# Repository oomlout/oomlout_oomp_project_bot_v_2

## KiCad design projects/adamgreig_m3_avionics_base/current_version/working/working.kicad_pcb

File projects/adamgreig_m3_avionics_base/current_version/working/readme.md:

# m3_avionics
 
## summary 
* id: adamgreig_m3_avionics_base
* user: adamgreig
* name: m3_avionics
* board: base
* repo: https://github.com/adamgreig/m3-avionics
* src_file_repo_kicad_pcb: m3base/base.kicad_pcb
* src_file_repo_kicad_pcb_link: https://github.com/adamgreig/m3-avionics/tree/master/m3base/base.kicad_pcb

* src_file_repo_sch: m3base/base.sch
* src_file_repo_sch_link: https://github.com/adamgreig/m3-avionics/tree/master/m3base/base.sch
* full details link: https://github.com/oomlout/oomlout_oomp_project_bot_v_2/tree/main/projects/adamgreig_m3_avionics_base/current_version/working  

## schematic  
  
[schematic (pdf)](working_schematic.pdf) 

## pcb  

[board (pdf)](working.pdf)  

## working_bom
| Id | Designator | Footprint | Quantity | Designation | Supplier and ref |  | None | 
| --- | --- | --- | --- | --- | --- | --- | --- | 
| 1 | C4,C5 | 0603-L | 2 | 2u2 |  |  | [''] | 
| 2 | C6 | 0603-L | 1 | 1u |  |  | [''] | 
| 3 | C7,C8,C11,C12,C13,C16,C1 | 0603-L | 7 | 100n |  |  | [''] | 
| 4 | R2 | 0603-L | 1 | 4K7 |  |  | [''] | 
| 5 | R3 | 0603-L | 1 | 10K |  |  | [''] | 
| 6 | C2,C3 | 0603-L | 2 | 10p |  |  | [''] | 
| 7 | IC1 | LQFP-64 | 1 | STM32F405RxTx |  |  | [''] | 
| 8 | IC2 | DFN-8-EP-MICROCHIP | 1 | MCP2562 |  |  | [''] | 
| 9 | J1 | TFML-110-02-L-D | 1 | WEST TOP |  |  | [''] | 
| 10 | J2 | TFML-110-02-L-D | 1 | EAST TOP |  |  | [''] | 
| 11 | R1 | 0603-L | 1 | 100R |  |  | [''] | 
| 12 | R5 | 0603-L | 1 | 120R |  |  | [''] | 
| 13 | Y1 | XTAL-20x16 | 1 | 26MHz |  |  | [''] | 
| 14 | D1,D2,D3,D4,D5,D6,D7,D8,D9,D10,D11,D12 | 0402 | 12 | ESD_DIODE |  |  | [''] | 
| 15 | C15 | 0603-L | 1 | 4u7 |  |  | [''] | 
| 16 | J5 | B02B-PASK | 1 | PYRO1 |  |  | [''] | 
| 17 | J6 | B02B-PASK | 1 | PYRO3 |  |  | [''] | 
| 18 | J7 | B02B-PASK | 1 | ARM |  |  | [''] | 
| 19 | J8 | B02B-PASK | 1 | PYRO2 |  |  | [''] | 
| 20 | J9 | B02B-PASK | 1 | PYRO4 |  |  | [''] | 
| 21 | J10 | B02B-PASK | 1 | PWR |  |  | [''] | 
| 22 | J11 | B02B-PASK | 1 | CHG |  |  | [''] | 
| 23 | J12 | B02B-PASK | 1 | CAM |  |  | [''] | 
| 24 | J13 | B04B-PASK | 1 | USB |  |  | [''] | 
| 25 | P1 | TC2030-NL | 1 | SWD_TC |  |  | [''] | 
| 26 | R4 | 0603-L | 1 | 1K |  |  | [''] | 

## bom_schematic
| Ref | Qnty | Value | Cmp name | Footprint | Description | Vendor | DNP | 
| --- | --- | --- | --- | --- | --- | --- | --- | 
| C1, C7, C8, C11, C12, C13, C16 | 7 | 100n | C_Small | Capacitors_SMD:C_0603 |  |  |  | 
| C2, C3 | 2 | 10p | C_Small | Capacitors_SMD:C_0603 |  |  |  | 
| C4, C5 | 2 | 2u2 | C_Small | Capacitors_SMD:C_0603 |  |  |  | 
| C6 | 1 | 1u | C_Small | Capacitors_SMD:C_0603 |  |  |  | 
| C15 | 1 | 4u7 | C_Small | Capacitors_SMD:C_0603 |  |  |  | 
| D1, D2, D3, D4, D5, D6, D7, D8, D9, D10, D11, D12 | 12 | ESD_DIODE | ESD_DIODE | agg:0402 |  |  |  | 
| IC1 | 1 | STM32F405RxTx | STM32F405RxTx | agg:LQFP-64 |  |  |  | 
| IC2 | 1 | MCP2562 | MCP2562 | agg:DFN-8-EP-MICROCHIP |  |  |  | 
| J1 | 1 | WEST TOP | CONN_02x10 | agg:TFML-110-02-L-D |  |  |  | 
| J2 | 1 | EAST TOP | CONN_02x10 | agg:TFML-110-02-L-D |  |  |  | 
| J5 | 1 | PYRO1 | CONN_01x02 | agg:B02B-PASK |  |  |  | 
| J6 | 1 | PYRO3 | CONN_01x02 | agg:B02B-PASK |  |  |  | 
| J7 | 1 | ARM | CONN_01x02 | agg:B02B-PASK |  |  |  | 
| J8 | 1 | PYRO2 | CONN_01x02 | agg:B02B-PASK |  |  |  | 
| J9 | 1 | PYRO4 | CONN_01x02 | agg:B02B-PASK |  |  |  | 
| J10 | 1 | PWR | CONN_01x02 | agg:B02B-PASK |  |  |  | 
| J11 | 1 | CHG | CONN_01x02 | agg:B02B-PASK |  |  |  | 
| J12 | 1 | CAM | CONN_01x02 | agg:B02B-PASK |  |  |  | 
| J13 | 1 | USB | CONN_01x04 | agg:B04B-PASK |  |  |  | 
| P1 | 1 | SWD_TC | SWD_TC | agg:TC2030-NL |  |  |  | 
| R1 | 1 | 100R | R | Resistors_SMD:R_0603 |  |  |  | 
| R2 | 1 | 4K7 | R | Resistors_SMD:R_0603 |  |  |  | 
| R3 | 1 | 10K | R | Resistors_SMD:R_0603 |  |  |  | 
| R4 | 1 | 1K | R | Resistors_SMD:R_0603 |  |  |  | 
| R5 | 1 | 120R | R | Resistors_SMD:R_0603 |  |  |  | 
| Y1 | 1 | 26MHz | XTAL | agg:XTAL-20x16 |  |  |  |

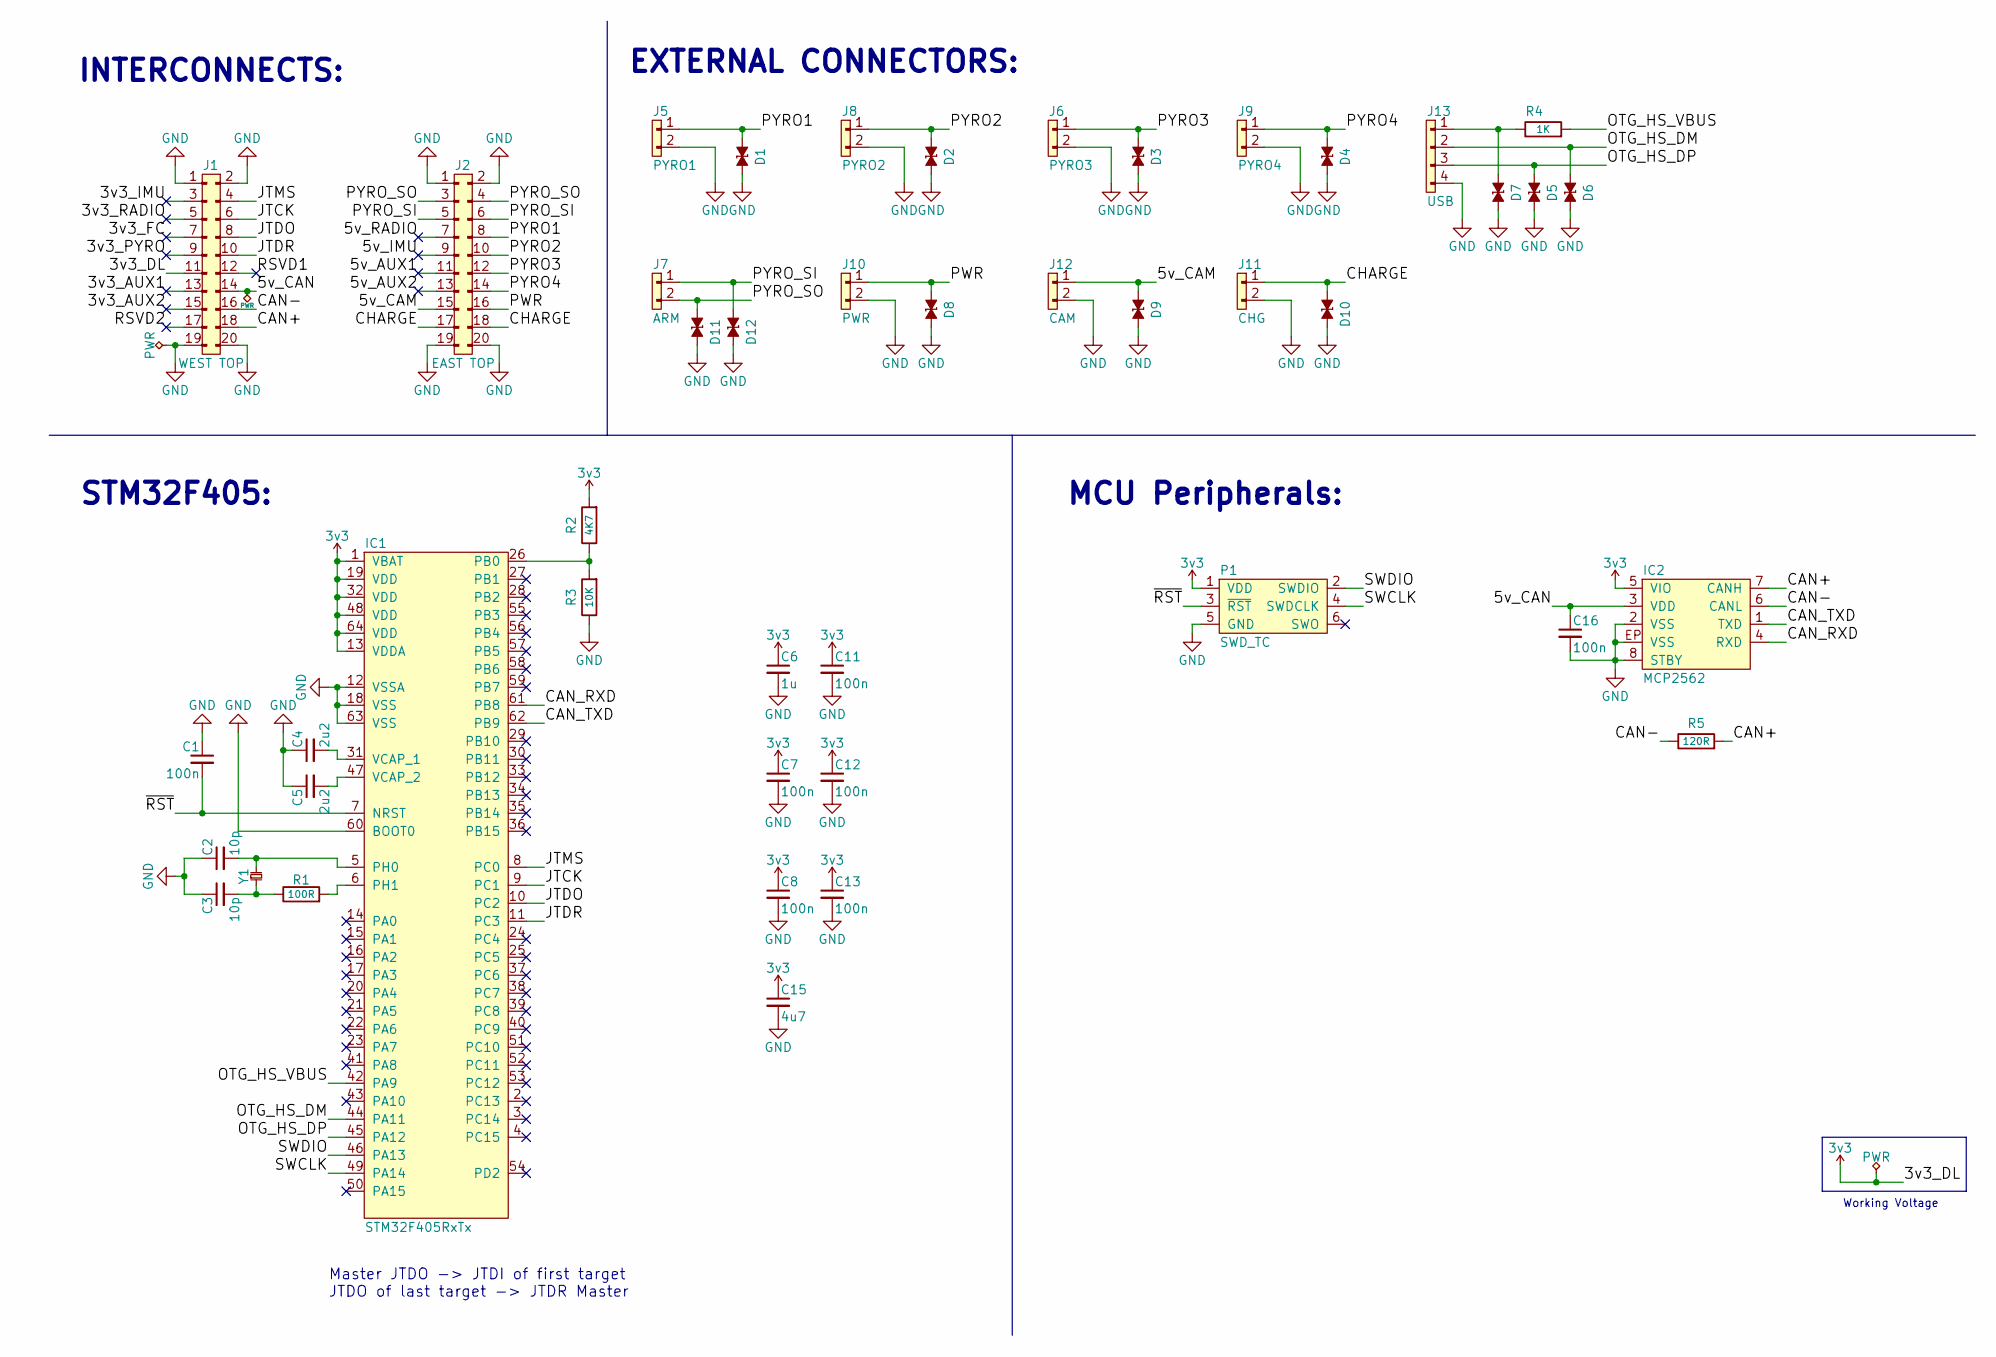
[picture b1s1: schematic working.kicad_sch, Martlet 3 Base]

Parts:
C1, C7, C8, C11, C12, C13, C16: 100n; C_0603; Farnell 2496834
C2, C3: 10p; C_0603; Farnell 2309035
C4, C5: 2u2; C_0603; Farnell 1797012
C6: 1u; C_0603; Farnell 1865556
C15: 4u7; C_0603; Farnell 2496930
D1, D2, D3, D4, D5, D6, D7, D8, D9, D10, D11, D12: ESD_DIODE; 0402; Farnell 2368169
IC1: STM32F405RxTx; LQFP-64; Farnell 2064363
IC2: MCP2562; DFN-8-EP-MICROCHIP; Farnell 2448755
J1: WEST TOP; TFML-110-02-L-D
J2: EAST TOP; TFML-110-02-L-D
J5: PYRO1; B02B-PASK; Farnell 1830734
J6: PYRO3; B02B-PASK; Farnell 1830734
J7: ARM; B02B-PASK; Farnell 1830734
J8: PYRO2; B02B-PASK; Farnell 1830734
J9: PYRO4; B02B-PASK; Farnell 1830734
J10: PWR; B02B-PASK; Farnell 1830734
J11: CHG; B02B-PASK; Farnell 1830734
J12: CAM; B02B-PASK; Farnell 1830734
J13: USB; B04B-PASK; Farnell 1830737
P1: SWD_TC; TC2030-NL
R1: 100R; R_0603; Farnell 2502395
R2: 4K7; R_0603; Farnell 2502463
R3: 10K; R_0603; Farnell 9238603
R4: 1K; R_0603; Farnell 2309108
R5: 120R; R_0603; Farnell 9238379
Y1: 26MHz; XTAL-20x16; Farnell 2506952

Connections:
3v3: C6.1, C7.1, C8.1, C11.1, C12.1, C13.1, C15.1, IC1.1 (VBAT), IC1.13 (VDDA), IC1.19 (VDD), IC1.32 (VDD), IC1.48 (VDD), IC1.64 (VDD), IC2.5 (VIO), J1.11, P1.1 (VDD), R2.2
/3v3_AUX1: J1.13
/3v3_AUX2: J1.15
/3v3_FC: J1.7
/3v3_IMU: J1.3
/3v3_PYRO: J1.9
/3v3_RADIO: J1.5
/5v_AUX1: J2.11
/5v_AUX2: J2.13
/5v_CAM: D9.1, J2.15, J12.1
/5v_CAN: C16.1, IC2.3 (VDD), J1.14
/5v_IMU: J2.9
/5v_RADIO: J2.7
/CAN+: IC2.7 (CANH), J1.18, R5.2
/CAN-: IC2.6 (CANL), J1.16, R5.1
/CAN_RXD: IC1.61 (PB8), IC2.4 (RXD)
/CAN_TXD: IC1.62 (PB9), IC2.1 (TXD)
/CHARGE: D10.1, J2.17, J2.18, J11.1
/JTCK: IC1.9 (PC1), J1.6
/JTDO: IC1.10 (PC2), J1.8
/JTDR: IC1.11 (PC3), J1.10
/JTMS: IC1.8 (PC0), J1.4
/OTG_HS_DM: D6.1, IC1.44 (PA11), J13.2
/OTG_HS_DP: D5.1, IC1.45 (PA12), J13.3
/OTG_HS_VBUS: IC1.42 (PA9), R4.2
/PWR: D8.1, J2.16, J10.1
/PYRO1: D1.1, J2.8, J5.1
/PYRO2: D2.1, J2.10, J8.1
/PYRO3: D3.1, J2.12, J6.1
/PYRO4: D4.1, J2.14, J9.1
/PYRO_SI: D12.1, J2.5, J2.6, J7.1
/PYRO_SO: D11.1, J2.3, J2.4, J7.2
/RSVD1: J1.12
/RSVD2: J1.17
/SWCLK: IC1.49 (PA14), P1.4 (SWDCLK)
/SWDIO: IC1.46 (PA13), P1.2 (SWDIO)
/~RST: C1.2, IC1.7 (NRST), P1.3 (~RST)
GND: C1.1, C2.1, C3.1, C4.1, C5.1, C6.2, C7.2, C8.2, C11.2, C12.2, C13.2, C15.2, C16.2, D1.2, D2.2, D3.2, D4.2, D5.2, D6.2, D7.2, D8.2, D9.2, D10.2, D11.2, D12.2, IC1.12 (VSSA), IC1.18 (VSS), IC1.60 (BOOT0), IC1.63 (VSS), IC2.2 (VSS), IC2.8 (STBY), IC2.EP (VSS), J1.1, J1.2, J1.19, J1.20, J2.1, J2.2, J2.19, J2.20, J5.2, J6.2, J8.2, J9.2, J10.2, J11.2, J12.2, J13.4, P1.5 (GND), R3.1
unnamed: C2.2, IC1.5 (PH0), Y1.2
unnamed: C3.2, R1.1, Y1.1
unnamed: C4.2, IC1.31 (VCAP_1)
unnamed: C5.2, IC1.47 (VCAP_2)
unnamed: D7.1, J13.1, R4.1
unnamed: IC1.6 (PH1), R1.2
unnamed: IC1.26 (PB0), R2.1, R3.2

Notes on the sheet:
STM32F405:
INTERCONNECTS:
MCU Peripherals:
EXTERNAL CONNECTORS:
Master JTDO -> JTDI of first target JTDO of last target -> JTDR Master
Working Voltage

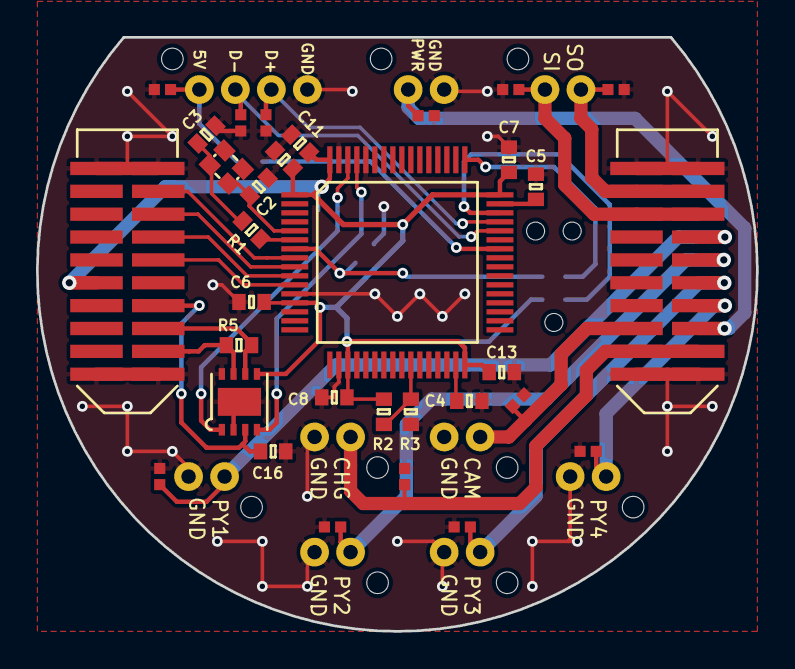
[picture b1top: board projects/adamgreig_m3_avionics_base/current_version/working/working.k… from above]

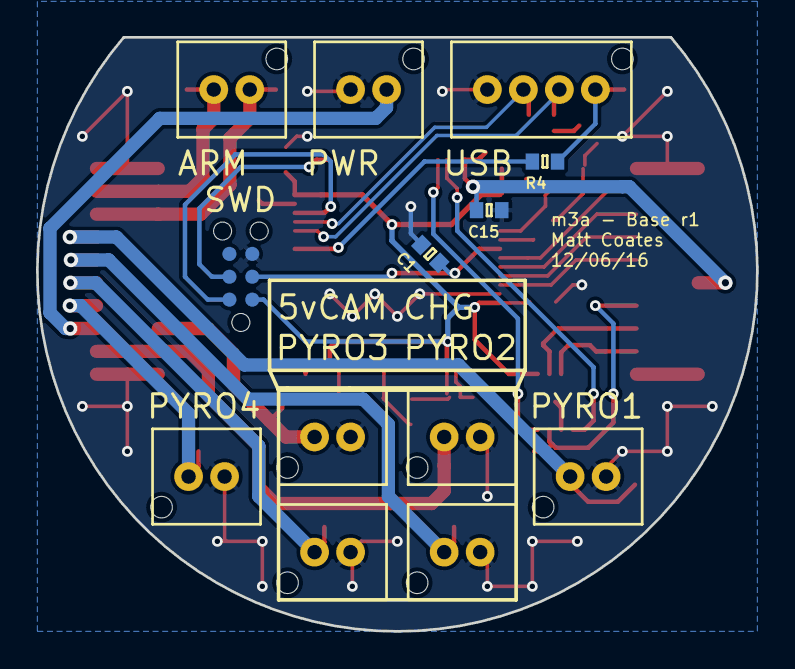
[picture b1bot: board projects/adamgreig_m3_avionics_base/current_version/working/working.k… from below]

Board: 2 copper layers, 40.0 x 33.0 mm, 45 parts (13 on the bottom side), 33 nets.

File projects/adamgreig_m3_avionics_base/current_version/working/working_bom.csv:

"Id";"Designator";"Footprint";"Quantity";"Designation";"Supplier and ref";
1;"C4,C5";"0603-L";2;"2u2";;;
2;"C6";"0603-L";1;"1u";;;
3;"C7,C8,C11,C12,C13,C16,C1";"0603-L";7;"100n";;;
4;"R2";"0603-L";1;"4K7";;;
5;"R3";"0603-L";1;"10K";;;
6;"C2,C3";"0603-L";2;"10p";;;
7;"IC1";"LQFP-64";1;"STM32F405RxTx";;;
8;"IC2";"DFN-8-EP-MICROCHIP";1;"MCP2562";;;
9;"J1";"TFML-110-02-L-D";1;"WEST TOP";;;
10;"J2";"TFML-110-02-L-D";1;"EAST TOP";;;
11;"R1";"0603-L";1;"100R";;;
12;"R5";"0603-L";1;"120R";;;
13;"Y1";"XTAL-20x16";1;"26MHz";;;
14;"D1,D2,D3,D4,D5,D6,D7,D8,D9,D10,D11,D12";"0402";12;"ESD_DIODE";;;
15;"C15";"0603-L";1;"4u7";;;
16;"J5";"B02B-PASK";1;"PYRO1";;;
17;"J6";"B02B-PASK";1;"PYRO3";;;
18;"J7";"B02B-PASK";1;"ARM";;;
19;"J8";"B02B-PASK";1;"PYRO2";;;
20;"J9";"B02B-PASK";1;"PYRO4";;;
21;"J10";"B02B-PASK";1;"PWR";;;
22;"J11";"B02B-PASK";1;"CHG";;;
23;"J12";"B02B-PASK";1;"CAM";;;
24;"J13";"B04B-PASK";1;"USB";;;
25;"P1";"TC2030-NL";1;"SWD_TC";;;
26;"R4";"0603-L";1;"1K";;;

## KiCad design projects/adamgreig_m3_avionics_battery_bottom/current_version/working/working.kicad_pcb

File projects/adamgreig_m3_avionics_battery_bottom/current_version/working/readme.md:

# m3_avionics
 
## summary 
* id: adamgreig_m3_avionics_battery_bottom
* user: adamgreig
* name: m3_avionics
* board: battery_bottom
* repo: https://github.com/adamgreig/m3-avionics
* src_file_repo_kicad_pcb: m3psu/pcb/Battery-Bottom/Battery-Bottom.kicad_pcb
* src_file_repo_kicad_pcb_link: https://github.com/adamgreig/m3-avionics/tree/master/m3psu/pcb/Battery-Bottom/Battery-Bottom.kicad_pcb

* src_file_repo_sch: m3psu/pcb/Battery-Bottom/Battery-Bottom.sch
* src_file_repo_sch_link: https://github.com/adamgreig/m3-avionics/tree/master/m3psu/pcb/Battery-Bottom/Battery-Bottom.sch
* full details link: https://github.com/oomlout/oomlout_oomp_project_bot_v_2/tree/main/projects/adamgreig_m3_avionics_battery_bottom/current_version/working  

## schematic  
  
[schematic (pdf)](working_schematic.pdf) 

## pcb  

[board (pdf)](working.pdf)  

## working_bom
| Id | Designator | Footprint | Quantity | Designation | Supplier and ref |  | None | 
| --- | --- | --- | --- | --- | --- | --- | --- | 
| 1 | J1 | Socket_Strip_Straight_1x01 | 1 | BATT_CENTRE_TAP |  |  | [''] | 
| 2 | J3 | TFML-110-02-L-D | 1 | WEST TOP |  |  | [''] | 
| 3 | J5 | TFML-110-02-L-D | 1 | EAST TOP |  |  | [''] | 
| 4 | J2 | Socket_Strip_Straight_1x02 | 1 | BATT |  |  | [''] | 
| 5 | J4 | SFML-110-02-L-D-LC | 1 | WEST BOT |  |  | [''] | 
| 6 | J6 | SFML-110-02-L-D-LC | 1 | EAST BOT |  |  | [''] | 
| 7 | J7 | SFML-105-02-L-D-LC | 1 | NORTH BOT |  |  | [''] | 

## bom_schematic
| Ref | Qnty | Value | Cmp name | Footprint | Description | Vendor | DNP | 
| --- | --- | --- | --- | --- | --- | --- | --- | 
| J1 | 1 | BATT_CENTRE_TAP | CONN_01x01 | Socket_Strips:Socket_Strip_Straight_1x01 |  |  |  | 
| J2 | 1 | BATT | CONN_01x02 | Socket_Strips:Socket_Strip_Straight_1x02 |  |  |  | 
| J3 | 1 | WEST TOP | CONN_02x10 | agg:TFML-110-02-L-D |  |  |  | 
| J4 | 1 | WEST BOT | CONN_02x10 | agg:SFML-110-02-L-D-LC |  |  |  | 
| J5 | 1 | EAST TOP | CONN_02x10 | agg:TFML-110-02-L-D |  |  |  | 
| J6 | 1 | EAST BOT | CONN_02x10 | agg:SFML-110-02-L-D-LC |  |  |  | 
| J7 | 1 | NORTH BOT | CONN_02x05 | agg:SFML-105-02-L-D-LC |  |  |  |

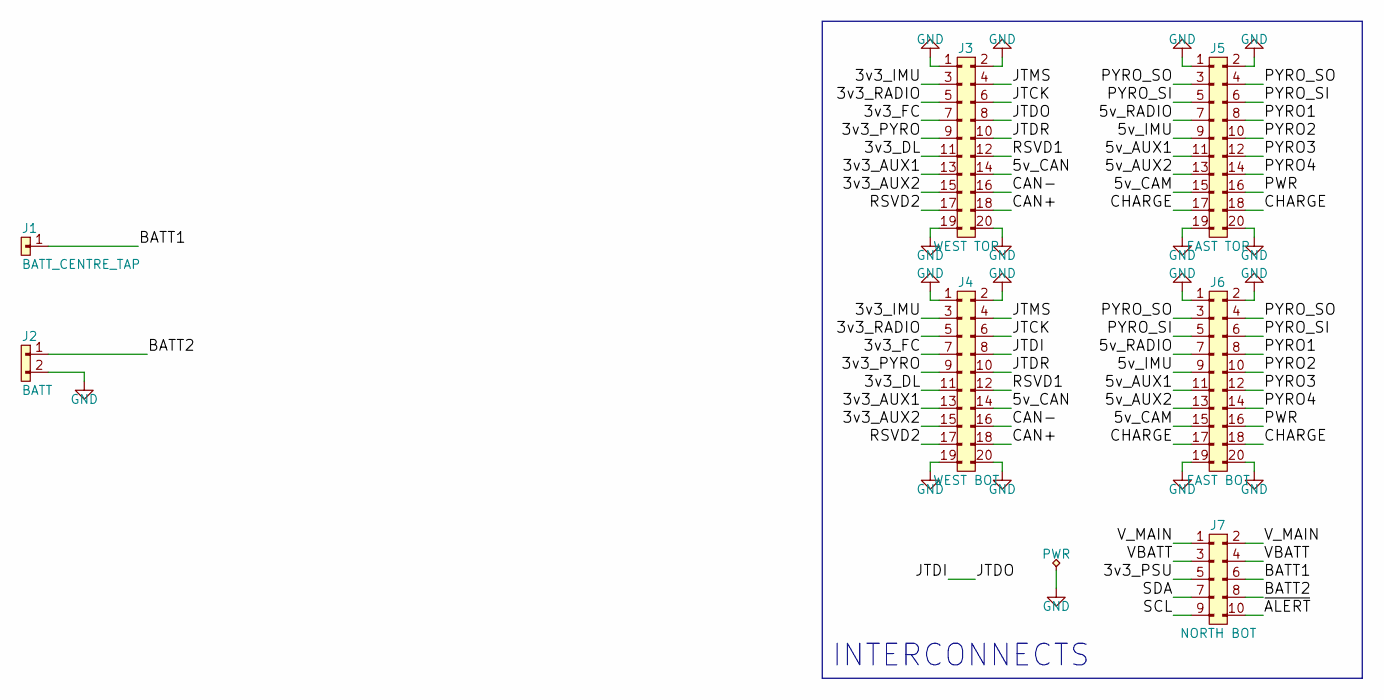
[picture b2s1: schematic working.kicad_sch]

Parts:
J1: BATT_CENTRE_TAP; Socket_Strip_Straight_1x01
J2: BATT; Socket_Strip_Straight_1x02
J3: WEST TOP; TFML-110-02-L-D
J4: WEST BOT; SFML-110-02-L-D-LC
J5: EAST TOP; TFML-110-02-L-D
J6: EAST BOT; SFML-110-02-L-D-LC
J7: NORTH BOT; SFML-105-02-L-D-LC

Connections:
/3v3_AUX1: J3.13, J4.13
/3v3_AUX2: J3.15, J4.15
/3v3_DL: J3.11, J4.11
/3v3_FC: J3.7, J4.7
/3v3_IMU: J3.3, J4.3
/3v3_PSU: J7.5
/3v3_PYRO: J3.9, J4.9
/3v3_RADIO: J3.5, J4.5
/5v_AUX1: J5.11, J6.11
/5v_AUX2: J5.13, J6.13
/5v_CAM: J5.15, J6.15
/5v_CAN: J3.14, J4.14
/5v_IMU: J5.9, J6.9
/5v_RADIO: J5.7, J6.7
/BATT1: J1.1, J7.6
/BATT2: J2.1, J7.8
/CAN+: J3.18, J4.18
/CAN-: J3.16, J4.16
/CHARGE: J5.17, J5.18, J6.17, J6.18
/JTCK: J3.6, J4.6
/JTDI: J3.8, J4.8
/JTDR: J3.10, J4.10
/JTMS: J3.4, J4.4
/PWR: J5.16, J6.16
/PYRO1: J5.8, J6.8
/PYRO2: J5.10, J6.10
/PYRO3: J5.12, J6.12
/PYRO4: J5.14, J6.14
/PYRO_SI: J5.5, J5.6, J6.5, J6.6
/PYRO_SO: J5.3, J5.4, J6.3, J6.4
/RSVD1: J3.12, J4.12
/RSVD2: J3.17, J4.17
/SCL: J7.9
/SDA: J7.7
/VBATT: J7.3, J7.4
/V_MAIN: J7.1, J7.2
/~ALERT: J7.10
GND: J2.2, J3.1, J3.2, J3.19, J3.20, J4.1, J4.2, J4.19, J4.20, J5.1, J5.2, J5.19, J5.20, J6.1, J6.2, J6.19, J6.20

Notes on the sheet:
INTERCONNECTS

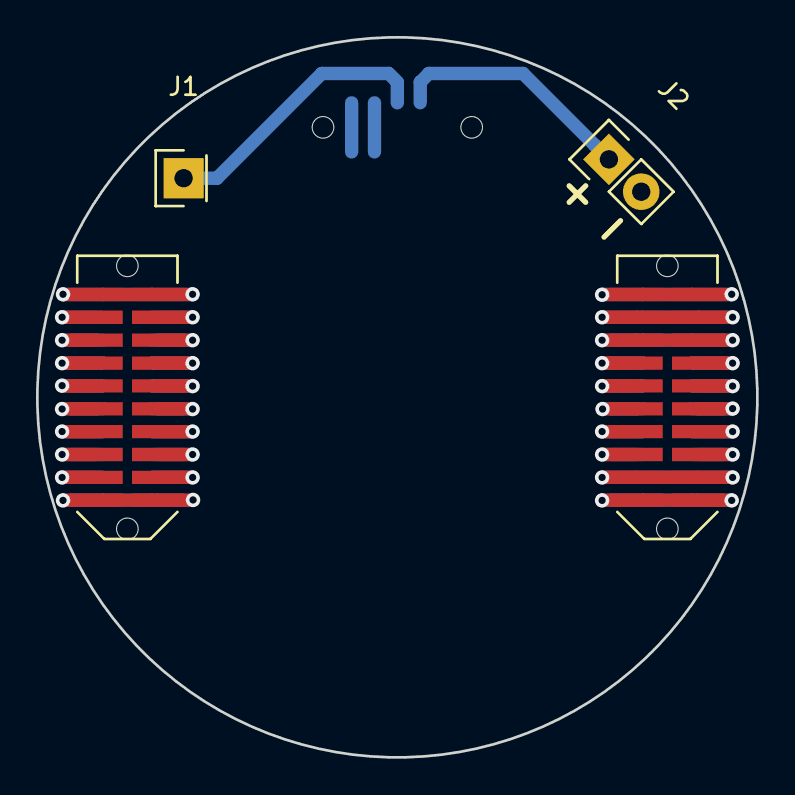
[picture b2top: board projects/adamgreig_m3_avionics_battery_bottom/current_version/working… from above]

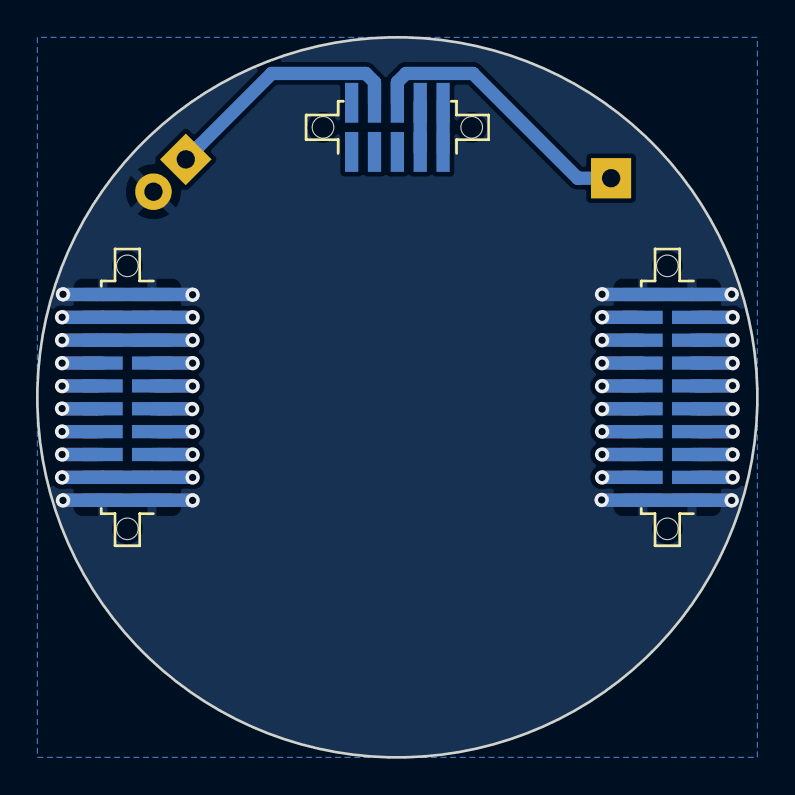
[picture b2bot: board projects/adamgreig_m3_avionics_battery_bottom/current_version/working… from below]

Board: 2 copper layers, 40.0 x 40.0 mm, 7 parts (3 on the bottom side), 34 nets.

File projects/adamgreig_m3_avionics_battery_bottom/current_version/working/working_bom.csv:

"Id";"Designator";"Footprint";"Quantity";"Designation";"Supplier and ref";
1;"J1";"Socket_Strip_Straight_1x01";1;"BATT_CENTRE_TAP";;;
2;"J3";"TFML-110-02-L-D";1;"WEST TOP";;;
3;"J5";"TFML-110-02-L-D";1;"EAST TOP";;;
4;"J2";"Socket_Strip_Straight_1x02";1;"BATT";;;
5;"J4";"SFML-110-02-L-D-LC";1;"WEST BOT";;;
6;"J6";"SFML-110-02-L-D-LC";1;"EAST BOT";;;
7;"J7";"SFML-105-02-L-D-LC";1;"NORTH BOT";;;

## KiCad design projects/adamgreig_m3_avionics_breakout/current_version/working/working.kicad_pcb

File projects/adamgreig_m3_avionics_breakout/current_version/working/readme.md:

# m3_avionics
 
## summary 
* id: adamgreig_m3_avionics_breakout
* user: adamgreig
* name: m3_avionics
* board: breakout
* repo: https://github.com/adamgreig/m3-avionics
* src_file_repo_kicad_pcb: m3dl/breakout/breakout.kicad_pcb
* src_file_repo_kicad_pcb_link: https://github.com/adamgreig/m3-avionics/tree/master/m3dl/breakout/breakout.kicad_pcb

* src_file_repo_sch: m3dl/breakout/breakout.sch
* src_file_repo_sch_link: https://github.com/adamgreig/m3-avionics/tree/master/m3dl/breakout/breakout.sch
* full details link: https://github.com/oomlout/oomlout_oomp_project_bot_v_2/tree/main/projects/adamgreig_m3_avionics_breakout/current_version/working  

## schematic  
  
[schematic (pdf)](working_schematic.pdf) 

## pcb  

[board (pdf)](working.pdf)  

## working_bom
| Id | Designator | Footprint | Quantity | Designation | Supplier and ref |  | None | 
| --- | --- | --- | --- | --- | --- | --- | --- | 
| 1 | J1 | TFML-110-02-L-D | 1 | WEST TOP |  |  | [''] | 
| 2 | J2 | TFML-110-02-L-D | 1 | EAST TOP |  |  | [''] | 
| 3 | J5 | S2B-EH | 1 | PYRO1 |  |  | [''] | 
| 4 | J6 | S2B-EH | 1 | PYRO3 |  |  | [''] | 
| 5 | J7 | S2B-EH | 1 | PYRO2 |  |  | [''] | 
| 6 | J8 | S2B-EH | 1 | PYRO4 |  |  | [''] | 
| 7 | J9 | S2B-EH | 1 | 5v_CAM |  |  | [''] | 
| 8 | D1,D2,D3,D4,D5 | 0402 | 5 | ESD_DIODE |  |  | [''] | 
| 9 | J3 | SFML-110-02-L-D-LC | 1 | WEST BOT |  |  | [''] | 
| 10 | J4 | SFML-110-02-L-D-LC | 1 | EAST BOT |  |  | [''] | 

## bom_schematic
| Ref | Qnty | Value | Cmp name | Footprint | Description | Vendor | DNP | 
| --- | --- | --- | --- | --- | --- | --- | --- | 
| D1, D2, D3, D4, D5 | 5 | ESD_DIODE | ESD_DIODE | agg:0402 |  |  |  | 
| J1 | 1 | WEST TOP | CONN_02x10 | agg:TFML-110-02-L-D |  |  |  | 
| J2 | 1 | EAST TOP | CONN_02x10 | agg:TFML-110-02-L-D |  |  |  | 
| J3 | 1 | WEST BOT | CONN_02x10 | agg:SFML-110-02-L-D-LC |  |  |  | 
| J4 | 1 | EAST BOT | CONN_02x10 | agg:SFML-110-02-L-D-LC |  |  |  | 
| J5 | 1 | PYRO1 | CONN_01x02 | agg:S2B-EH |  |  |  | 
| J6 | 1 | PYRO3 | CONN_01x02 | agg:S2B-EH |  |  |  | 
| J7 | 1 | PYRO2 | CONN_01x02 | agg:S2B-EH |  |  |  | 
| J8 | 1 | PYRO4 | CONN_01x02 | agg:S2B-EH |  |  |  | 
| J9 | 1 | 5v_CAM | CONN_01x02 | agg:S2B-EH |  |  |  |

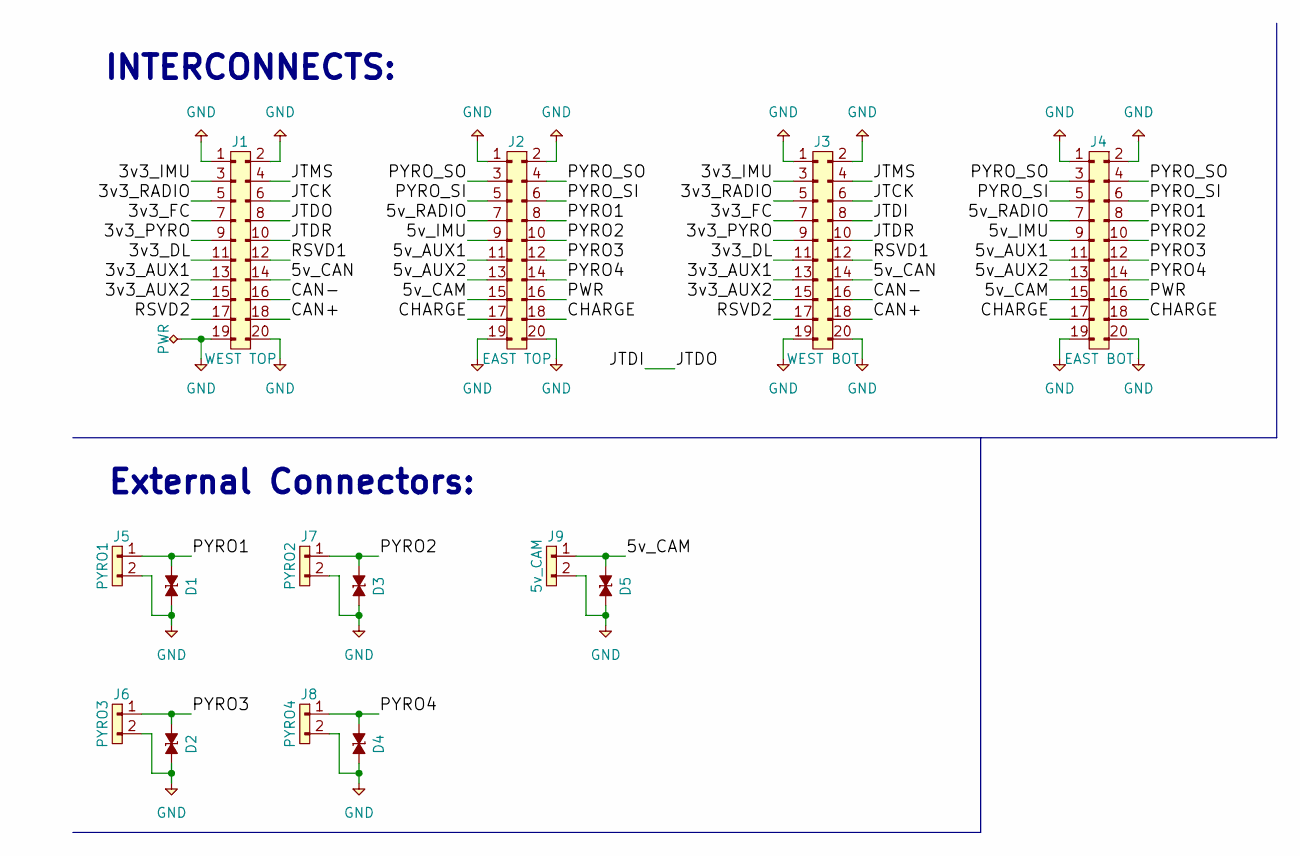
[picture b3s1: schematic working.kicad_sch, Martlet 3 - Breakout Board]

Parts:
D1, D2, D3, D4, D5: ESD_DIODE; 0402; Farnell 2368169
J1: WEST TOP; TFML-110-02-L-D
J2: EAST TOP; TFML-110-02-L-D
J3: WEST BOT; SFML-110-02-L-D-LC
J4: EAST BOT; SFML-110-02-L-D-LC
J5: PYRO1; S2B-EH
J6: PYRO3; S2B-EH
J7: PYRO2; S2B-EH
J8: PYRO4; S2B-EH
J9: 5v_CAM; S2B-EH

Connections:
/3v3_AUX1: J1.13, J3.13
/3v3_AUX2: J1.15, J3.15
/3v3_DL: J1.11, J3.11
/3v3_FC: J1.7, J3.7
/3v3_IMU: J1.3, J3.3
/3v3_PYRO: J1.9, J3.9
/3v3_RADIO: J1.5, J3.5
/5v_AUX1: J2.11, J4.11
/5v_AUX2: J2.13, J4.13
/5v_CAM: D5.1, J2.15, J4.15, J9.1
/5v_CAN: J1.14, J3.14
/5v_IMU: J2.9, J4.9
/5v_RADIO: J2.7, J4.7
/CAN+: J1.18, J3.18
/CAN-: J1.16, J3.16
/CHARGE: J2.17, J2.18, J4.17, J4.18
/JTCK: J1.6, J3.6
/JTDI: J1.8, J3.8
/JTDR: J1.10, J3.10
/JTMS: J1.4, J3.4
/PWR: J2.16, J4.16
/PYRO1: D1.1, J2.8, J4.8, J5.1
/PYRO2: D3.1, J2.10, J4.10, J7.1
/PYRO3: D2.1, J2.12, J4.12, J6.1
/PYRO4: D4.1, J2.14, J4.14, J8.1
/PYRO_SI: J2.5, J2.6, J4.5, J4.6
/PYRO_SO: J2.3, J2.4, J4.3, J4.4
/RSVD1: J1.12, J3.12
/RSVD2: J1.17, J3.17
GND: D1.2, D2.2, D3.2, D4.2, D5.2, J1.1, J1.2, J1.19, J1.20, J2.1, J2.2, J2.19, J2.20, J3.1, J3.2, J3.19, J3.20, J4.1, J4.2, J4.19, J4.20, J5.2, J6.2, J7.2, J8.2, J9.2

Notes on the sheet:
INTERCONNECTS:
External Connectors:

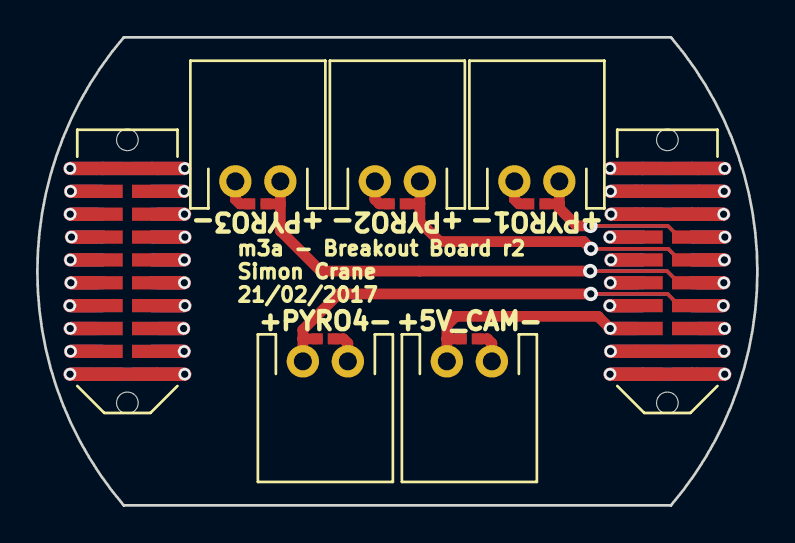
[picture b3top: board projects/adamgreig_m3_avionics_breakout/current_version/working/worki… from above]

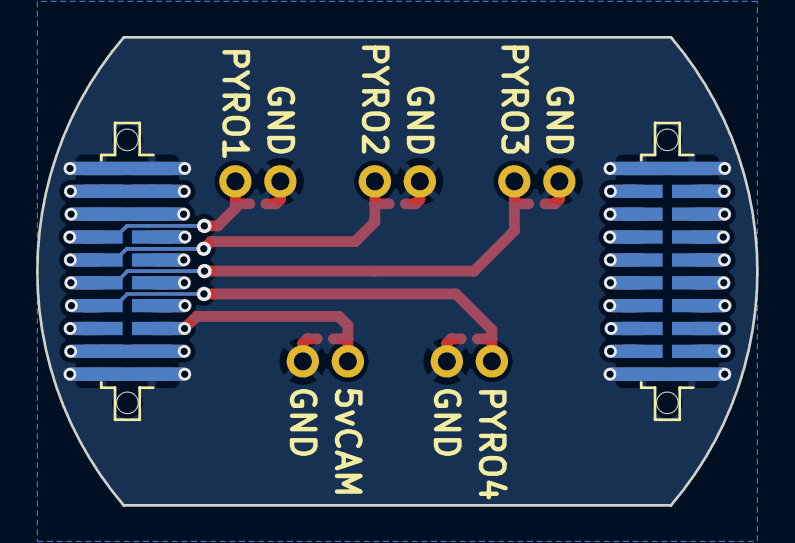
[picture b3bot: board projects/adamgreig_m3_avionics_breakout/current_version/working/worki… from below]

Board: 2 copper layers, 40.0 x 26.0 mm, 14 parts (2 on the bottom side), 30 nets.
